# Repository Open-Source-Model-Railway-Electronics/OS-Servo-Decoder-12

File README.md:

# OS-Servo-Decoder-12

TODO -> Fix pin nummering in source code and make the binary

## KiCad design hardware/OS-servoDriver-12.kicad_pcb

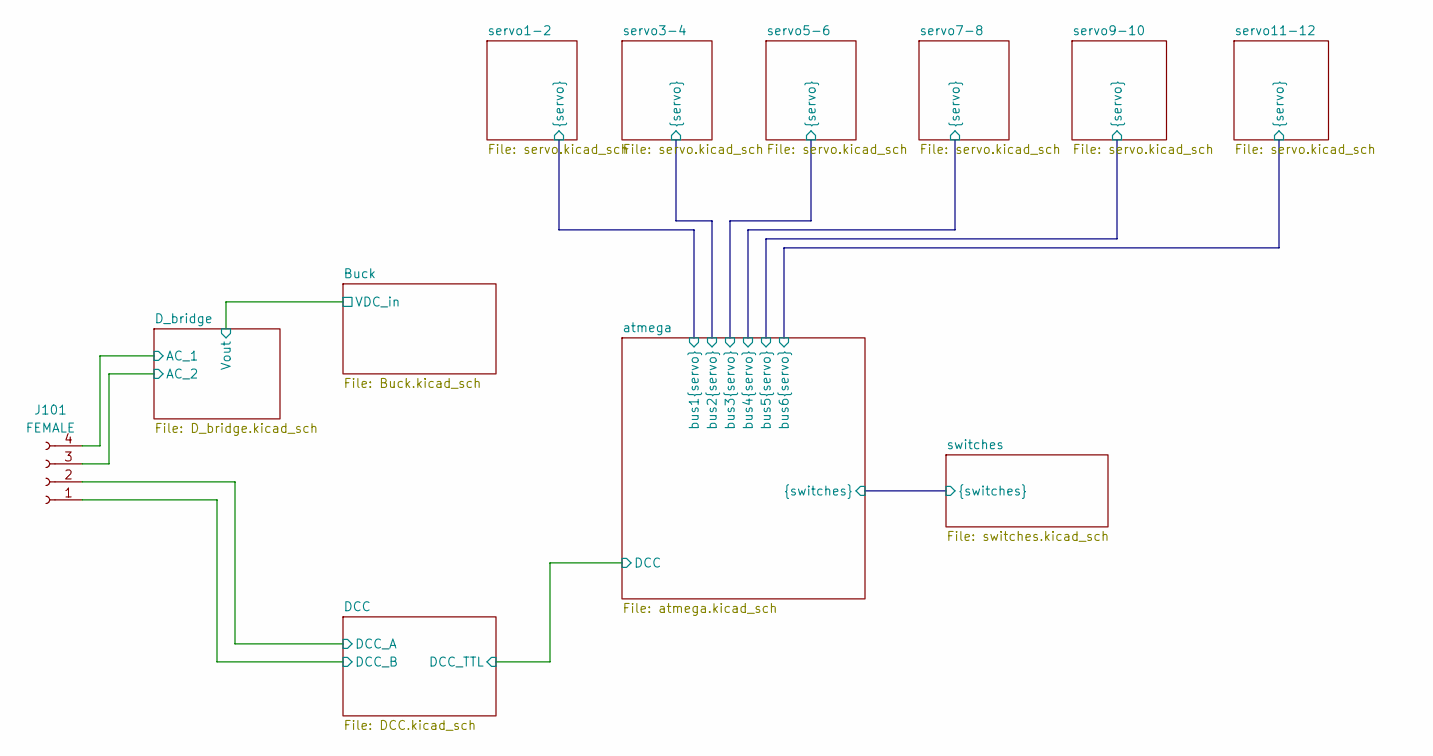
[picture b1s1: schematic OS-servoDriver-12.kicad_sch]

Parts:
J101: FEMALE; PhoenixContact_MC_1,5_4-G-3.5_1x04_P3.50mm_Horizontal

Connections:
/DCC/DCC_A: J101.2; also elsewhere on the board
/DCC/DCC_B: J101.1; also elsewhere on the board
/D_bridge/AC_1: J101.4; also elsewhere on the board
/D_bridge/AC_2: J101.3; also elsewhere on the board

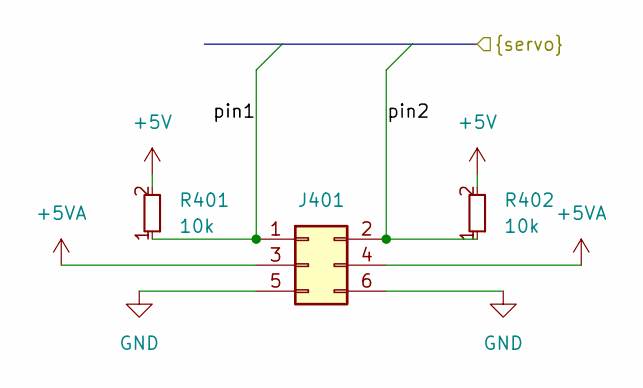
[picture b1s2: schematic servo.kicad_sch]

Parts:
J401: Conn_02x03_Odd_Even; PinHeader_2x03_P2.54mm_Vertical; JLCPCB Part# C65114
R401, R402: 10k; R_0603_smalltext; JLCPCB Part# C25804

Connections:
+5V: R401.2, R402.2; also elsewhere on the board
+5VA: J401.3, J401.4; also elsewhere on the board
/atmega/bus5.pin1: J401.1, R401.1; also elsewhere on the board
/atmega/bus5.pin2: J401.2, R402.1; also elsewhere on the board
GND: J401.5, J401.6; also elsewhere on the board

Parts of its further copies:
J701, J801, J901, J1001, J1201: Conn_02x03_Odd_Even; PinHeader_2x03_P2.54mm_Vertical; JLCPCB Part# C65114
R701, R702, R801, R802, R904, R905, R1004, R1005, R1201, R1202: 10k; R_0603_smalltext; JLCPCB Part# C25804

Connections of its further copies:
+5V: R701.2, R702.2, R801.2, R802.2, R904.2, R905.2, R1004.2, R1005.2, R1201.2, R1202.2; also elsewhere on the board
+5VA: J701.3, J701.4, J801.3, J801.4, J901.3, J901.4, J1001.3, J1001.4, J1201.3, J1201.4; also elsewhere on the board
/atmega/bus1.pin1: J701.1, R701.1; also elsewhere on the board
/atmega/bus1.pin2: J701.2, R702.1; also elsewhere on the board
/atmega/bus2.pin1: J801.1, R801.1; also elsewhere on the board
/atmega/bus2.pin2: J801.2, R802.1; also elsewhere on the board
/atmega/bus3.pin1: J901.1, R904.1; also elsewhere on the board
/atmega/bus3.pin2: J901.2, R905.1; also elsewhere on the board
/atmega/bus4.pin1: J1001.1, R1004.1; also elsewhere on the board
/atmega/bus4.pin2: J1001.2, R1005.1; also elsewhere on the board
/atmega/bus6.pin1: J1201.1, R1201.1; also elsewhere on the board
/atmega/bus6.pin2: J1201.2, R1202.1; also elsewhere on the board
GND: J701.5, J701.6, J801.5, J801.6, J901.5, J901.6, J1001.5, J1001.6, J1201.5, J1201.6; also elsewhere on the board

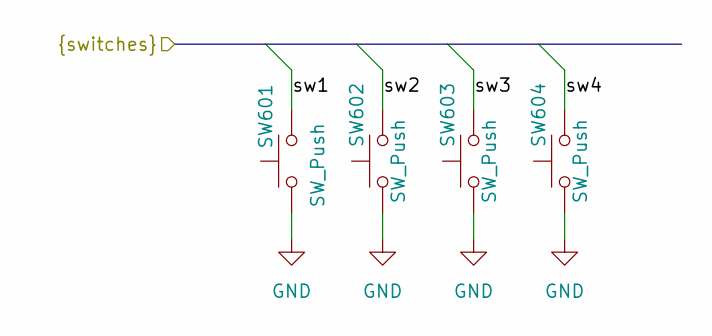
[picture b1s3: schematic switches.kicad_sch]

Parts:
SW601, SW602, SW603, SW604: SW_Push; tactile_SMD_6mm; JLCPCB Part# C294567

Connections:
/atmega/sw1: SW601.2; also elsewhere on the board
/atmega/sw2: SW602.2; also elsewhere on the board
/atmega/sw3: SW603.2; also elsewhere on the board
/atmega/sw4: SW604.2; also elsewhere on the board
GND: SW601.1, SW602.1, SW603.1, SW604.1; also elsewhere on the board

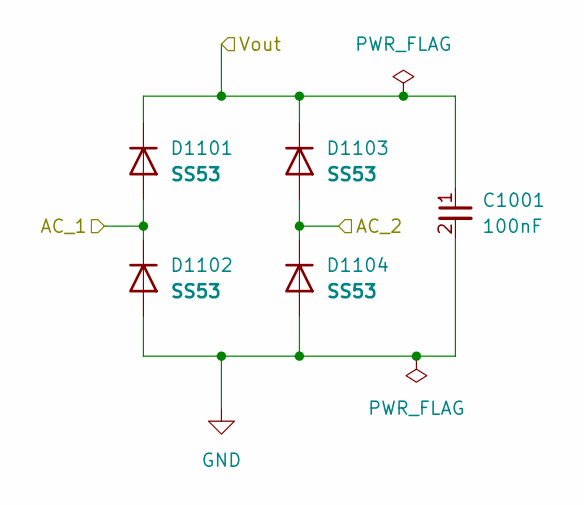
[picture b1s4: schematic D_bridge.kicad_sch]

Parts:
C1001: 100nF; C_0603_1608Metric; JLCPCB Part# C14663
D1101, D1102, D1103, D1104: SS53; D_SMA; JLCPCB Part# C8678

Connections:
/Buck/VDC_in: C1001.1, D1101.1 (K), D1103.1 (K); also elsewhere on the board
/D_bridge/AC_1: D1101.2 (A), D1102.1 (K); also elsewhere on the board
/D_bridge/AC_2: D1103.2 (A), D1104.1 (K); also elsewhere on the board
GND: C1001.2, D1102.2 (A), D1104.2 (A); also elsewhere on the board

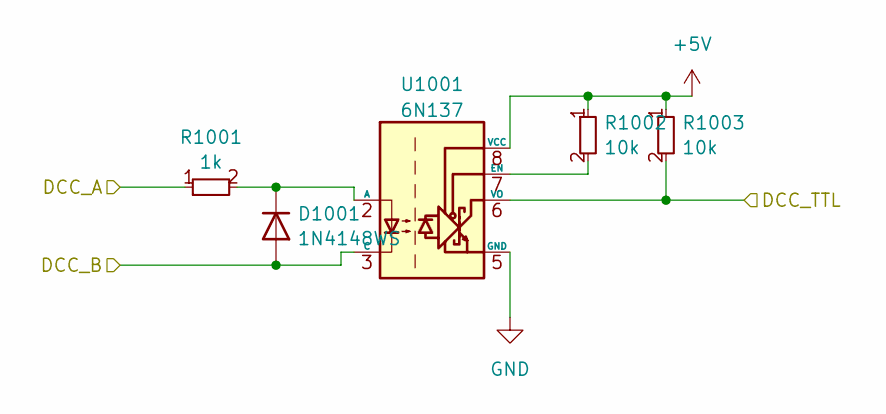
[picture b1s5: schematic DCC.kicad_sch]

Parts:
D1001: 1N4148WS; D_SOD-323; JLCPCB Part# C2128
R1001: 1k; R_0603_smalltext; JLCPCB Part# C21190
R1002, R1003: 10k; R_0603_smalltext; JLCPCB Part# C25804
U1001: 6N137; SOP-8_6.62x9.15mm_P2.54mm; JLCPCB Part# C110020

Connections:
+5V: R1002.1, R1003.1, U1001.8 (VCC); also elsewhere on the board
/DCC/DCC_A: R1001.1; also elsewhere on the board
/DCC/DCC_B: D1001.2 (A), U1001.3 (C); also elsewhere on the board
/DCC/DCC_TTL: R1003.2, U1001.6 (VO); also elsewhere on the board
GND: U1001.5 (GND); also elsewhere on the board
unnamed: D1001.1 (K), R1001.2, U1001.2 (A)
unnamed: R1002.2, U1001.7 (EN)

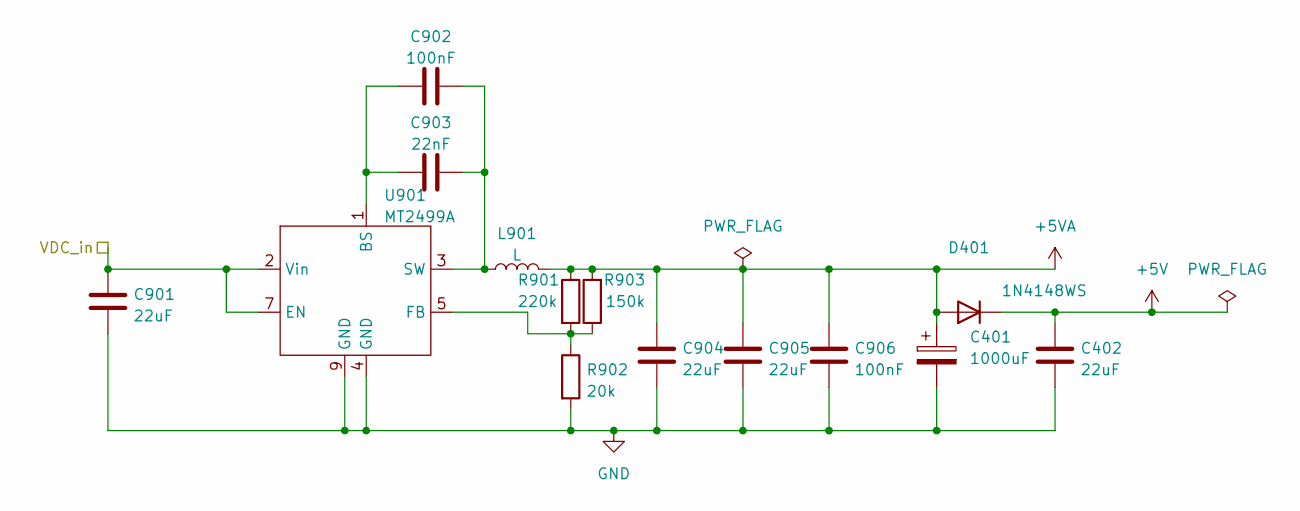
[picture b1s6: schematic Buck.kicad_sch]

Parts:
C401: 1000uF; CP_Elec_8x10.5; JLCPCB Part# C5162347
C402, C901, C904, C905: 22uF; C_0603_1608Metric; JLCPCB Part# C45783
C902, C906: 100nF; C_0402_1005Metric; JLCPCB Part# C307331
C903: 22nF; C_0402_1005Metric; JLCPCB Part# C1532
D401: 1N4148WS; D_SOD-323; JLCPCB Part# C2128
L901: L; L_Bourns-SRN8040_8x8.15mm; JLCPCB Part# C2929438
R901: 220k; R_0603_1608Metric; JLCPCB Part# C22961
R902: 20k; R_0603_1608Metric; JLCPCB Part# C4328
R903: 150k; R_0603_1608Metric; JLCPCB Part# C22807
U901: MT2499A; TI_SO-PowerPAD-8; JLCPCB Part# C3007555

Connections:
+5V: C402.1, D401.1 (K); also elsewhere on the board
+5VA: C401.1, C904.1, C905.1, C906.1, D401.2 (A), L901.2, R901.1, R903.2; also elsewhere on the board
/Buck/VDC_in: C901.1, U901.2 (Vin), U901.7 (EN); also elsewhere on the board
GND: C401.2, C402.2, C901.2, C904.2, C905.2, C906.2, R902.2, U901.4 (GND), U901.9 (GND); also elsewhere on the board
unnamed: C902.1, C903.1, U901.1 (BS)
unnamed: R901.2, R902.1, R903.1, U901.5 (FB)
unnamed: C902.2, C903.2, L901.1, U901.3 (SW)

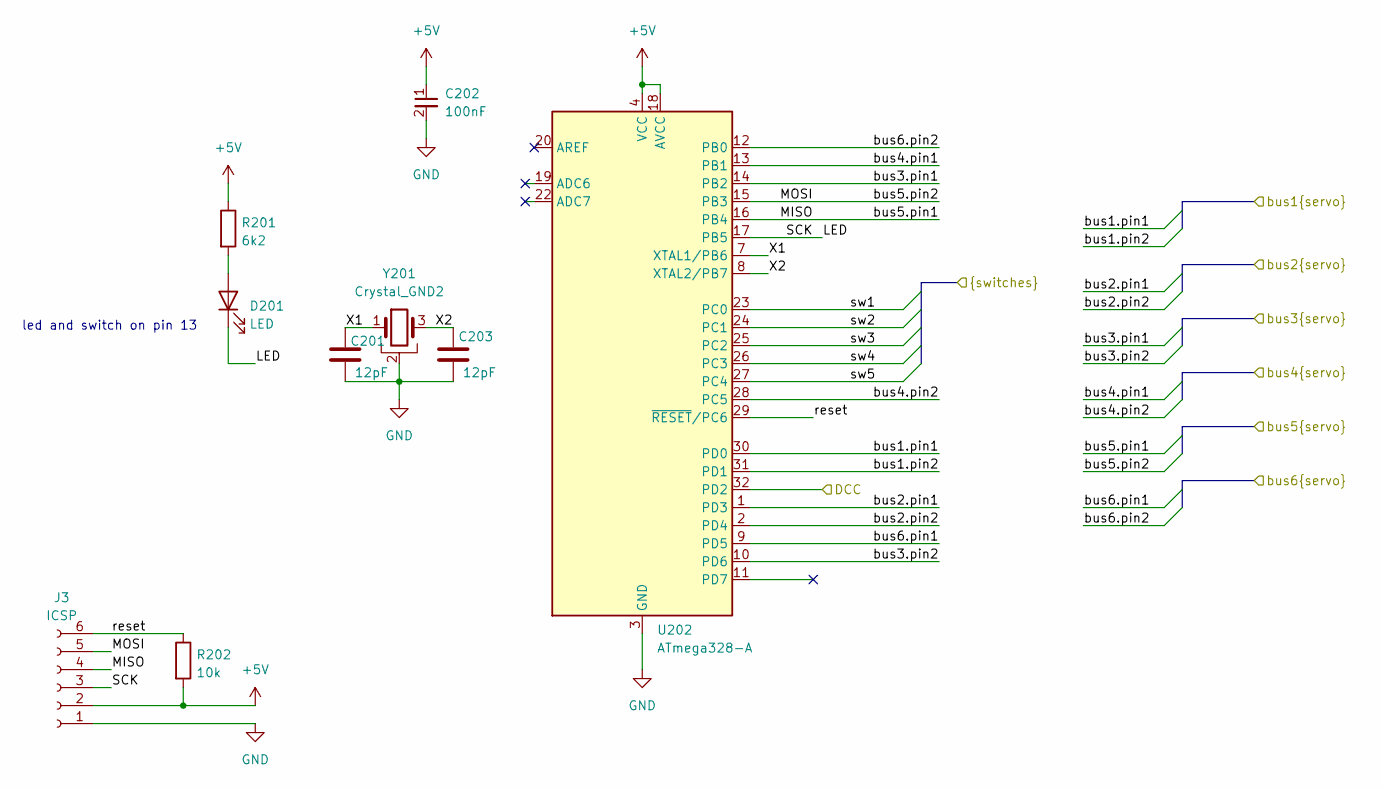
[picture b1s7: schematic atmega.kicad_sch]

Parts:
C201, C203: 12pF; C_0603_1608Metric; JLCPCB Part# C38523
C202: 100nF; C_0402_1005Metric; JLCPCB Part# C307331
D201: LED; LED_0805_2012Metric_Pad1.15x1.40mm_HandSolder; JLCPCB Part# C84256
J3: ICSP; PinHeader_1x06_P2.54mm_Vertical
R201: 6k2; R_0603_1608Metric_Pad0.98x0.95mm_HandSolder; JLCPCB Part# C4260
R202: 10k; R_0402_1005Metric_Pad0.72x0.64mm_HandSolder; JLCPCB Part# C25744
U202: ATmega328-A; TQFP-32_7x7mm_P0.8mm; JLCPCB Part# C14877
Y201: Crystal_GND2; crystal_arduino; JLCPCB Part# C13738

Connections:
+5V: C202.1, R201.1, R202.2, U202.4 (VCC), U202.6 (VCC), U202.18 (AVCC); also elsewhere on the board
/DCC/DCC_TTL: U202.32 (PD2); also elsewhere on the board
/atmega/LED: D201.1 (K), U202.17 (PB5); also elsewhere on the board
/atmega/X1: C201.2, U202.7 (XTAL1/PB6), Y201.1
/atmega/X2: C203.2, U202.8 (XTAL2/PB7), Y201.3
/atmega/bus1.pin1: U202.30 (PD0); also elsewhere on the board
/atmega/bus1.pin2: U202.31 (PD1); also elsewhere on the board
/atmega/bus2.pin1: U202.1 (PD3); also elsewhere on the board
/atmega/bus2.pin2: U202.2 (PD4); also elsewhere on the board
/atmega/bus3.pin1: U202.14 (PB2); also elsewhere on the board
/atmega/bus3.pin2: U202.10 (PD6); also elsewhere on the board
/atmega/bus4.pin1: U202.13 (PB1); also elsewhere on the board
/atmega/bus4.pin2: U202.28 (PC5); also elsewhere on the board
/atmega/bus5.pin1: U202.16 (PB4); also elsewhere on the board
/atmega/bus5.pin2: U202.15 (PB3); also elsewhere on the board
/atmega/bus6.pin1: U202.9 (PD5); also elsewhere on the board
/atmega/bus6.pin2: U202.12 (PB0); also elsewhere on the board
/atmega/reset: R202.1, U202.29 (~RESET/PC6); also elsewhere on the board
/atmega/sw1: U202.23 (PC0); also elsewhere on the board
/atmega/sw2: U202.24 (PC1); also elsewhere on the board
/atmega/sw3: U202.25 (PC2); also elsewhere on the board
/atmega/sw4: U202.26 (PC3); also elsewhere on the board
/atmega/sw5: U202.27 (PC4)
GND: C201.1, C202.2, C203.1, U202.3 (GND), U202.5 (GND), U202.21 (GND), Y201.2 (GND), Y201.4 (GND); also elsewhere on the board
unnamed: D201.2 (A), R201.2

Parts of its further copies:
J201: ICSP; PinHeader_1x06_P2.54mm_Vertical

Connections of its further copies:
+5V: J201.2; also elsewhere on the board
/atmega/LED: J201.3; also elsewhere on the board
/atmega/bus5.pin1: J201.4; also elsewhere on the board
/atmega/bus5.pin2: J201.5; also elsewhere on the board
/atmega/reset: J201.6; also elsewhere on the board
GND: J201.1; also elsewhere on the board

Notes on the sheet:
led and switch on pin 13

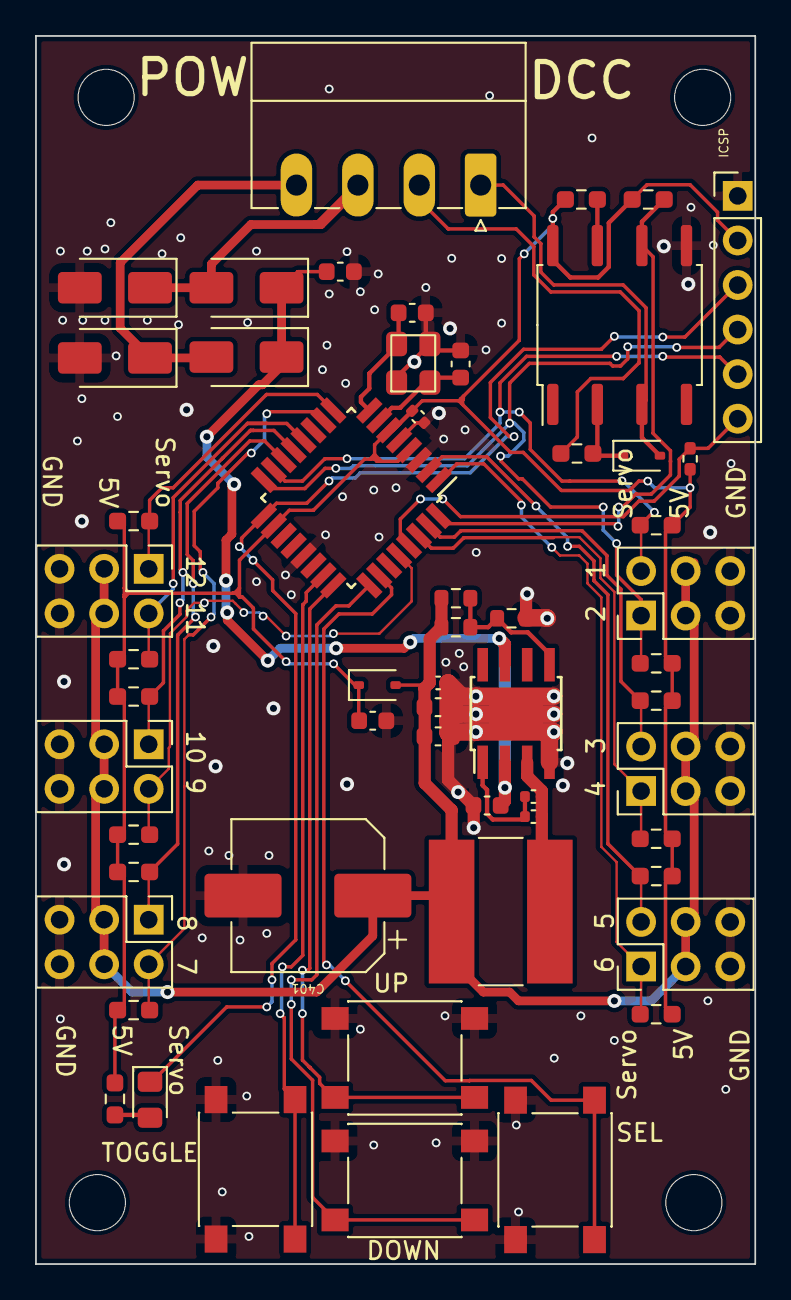
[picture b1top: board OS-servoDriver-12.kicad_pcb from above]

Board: 2 copper layers, 41.0 x 70.0 mm, 56 parts (0 on the bottom side), 35 nets.

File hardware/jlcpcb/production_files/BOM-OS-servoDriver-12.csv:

Comment,Designator,Footprint,LCSC
6N137,U1001,SOP-8_6.62x9.15mm_P2.54mm,C110020
Crystal_GND2,Y201,crystal_arduino,C13738
100nF,C1001,C_0603_1608Metric,C14663
ATmega328-A,U202,TQFP-32_7x7mm_P0.8mm,C14877
22nF,C903,C_0402_1005Metric,C1532
1k,R1001,R_0603_smalltext,C21190
1N4148WS,"D1001,D401",D_SOD-323,C2128
150k,R903,R_0603_1608Metric,C22807
220k,R901,R_0603_1608Metric,C22961
10k,R202,R_0402_1005Metric_Pad0.72x0.64mm_HandSolder,C25744
10k,"R1002,R1003,R1004,R1005,R1201,R1202,R401,R402,R701,R702,R801,R802,R904,R905",R_0603_smalltext,C25804
L,L901,L_Bourns-SRN8040_8x8.15mm,C2929438
SW_Push,"SW601,SW602,SW603,SW604",tactile_SMD_6mm,C294567
MT2499A,U901,TI_SO-PowerPAD-8,C3007555
100nF,"C202,C902,C906",C_0402_1005Metric,C307331
12pF,"C201,C203",C_0603_1608Metric,C38523
6k2,R201,R_0603_1608Metric_Pad0.98x0.95mm_HandSolder,C4260
20k,R902,R_0603_1608Metric,C4328
22uF,"C402,C901,C904,C905",C_0603_1608Metric,C45783
1000uF,C401,CP_Elec_8x10.5,C5162347
Conn_02x03_Odd_Even,"J1001,J1201,J401,J701,J801,J901",PinHeader_2x03_P2.54mm_Vertical,C65114
LED,D201,LED_0805_2012Metric_Pad1.15x1.40mm_HandSolder,C84256
SS53,"D1101,D1102,D1103,D1104",D_SMA,C8678
ICSP,J201,PinHeader_1x06_P2.54mm_Vertical,
FEMALE,J101,"PhoenixContact_MC_1,5_4-G-3.5_1x04_P3.50mm_Horizontal",

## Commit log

2025-06-17 added release preview files
2025-06-18 Remove misplaced submodule
2025-06-18 Removed .gitmodules
2025-06-18 added PCB files
2025-06-18 Moved submodule to 'software/'
2025-06-18 Updated software core version
2025-06-18 Pulled updated core submodule
2025-06-19 Toegevoegd: handleiding (manual.odt)
2025-06-19 Hersteld: handleiding toegevoegd in docs/
